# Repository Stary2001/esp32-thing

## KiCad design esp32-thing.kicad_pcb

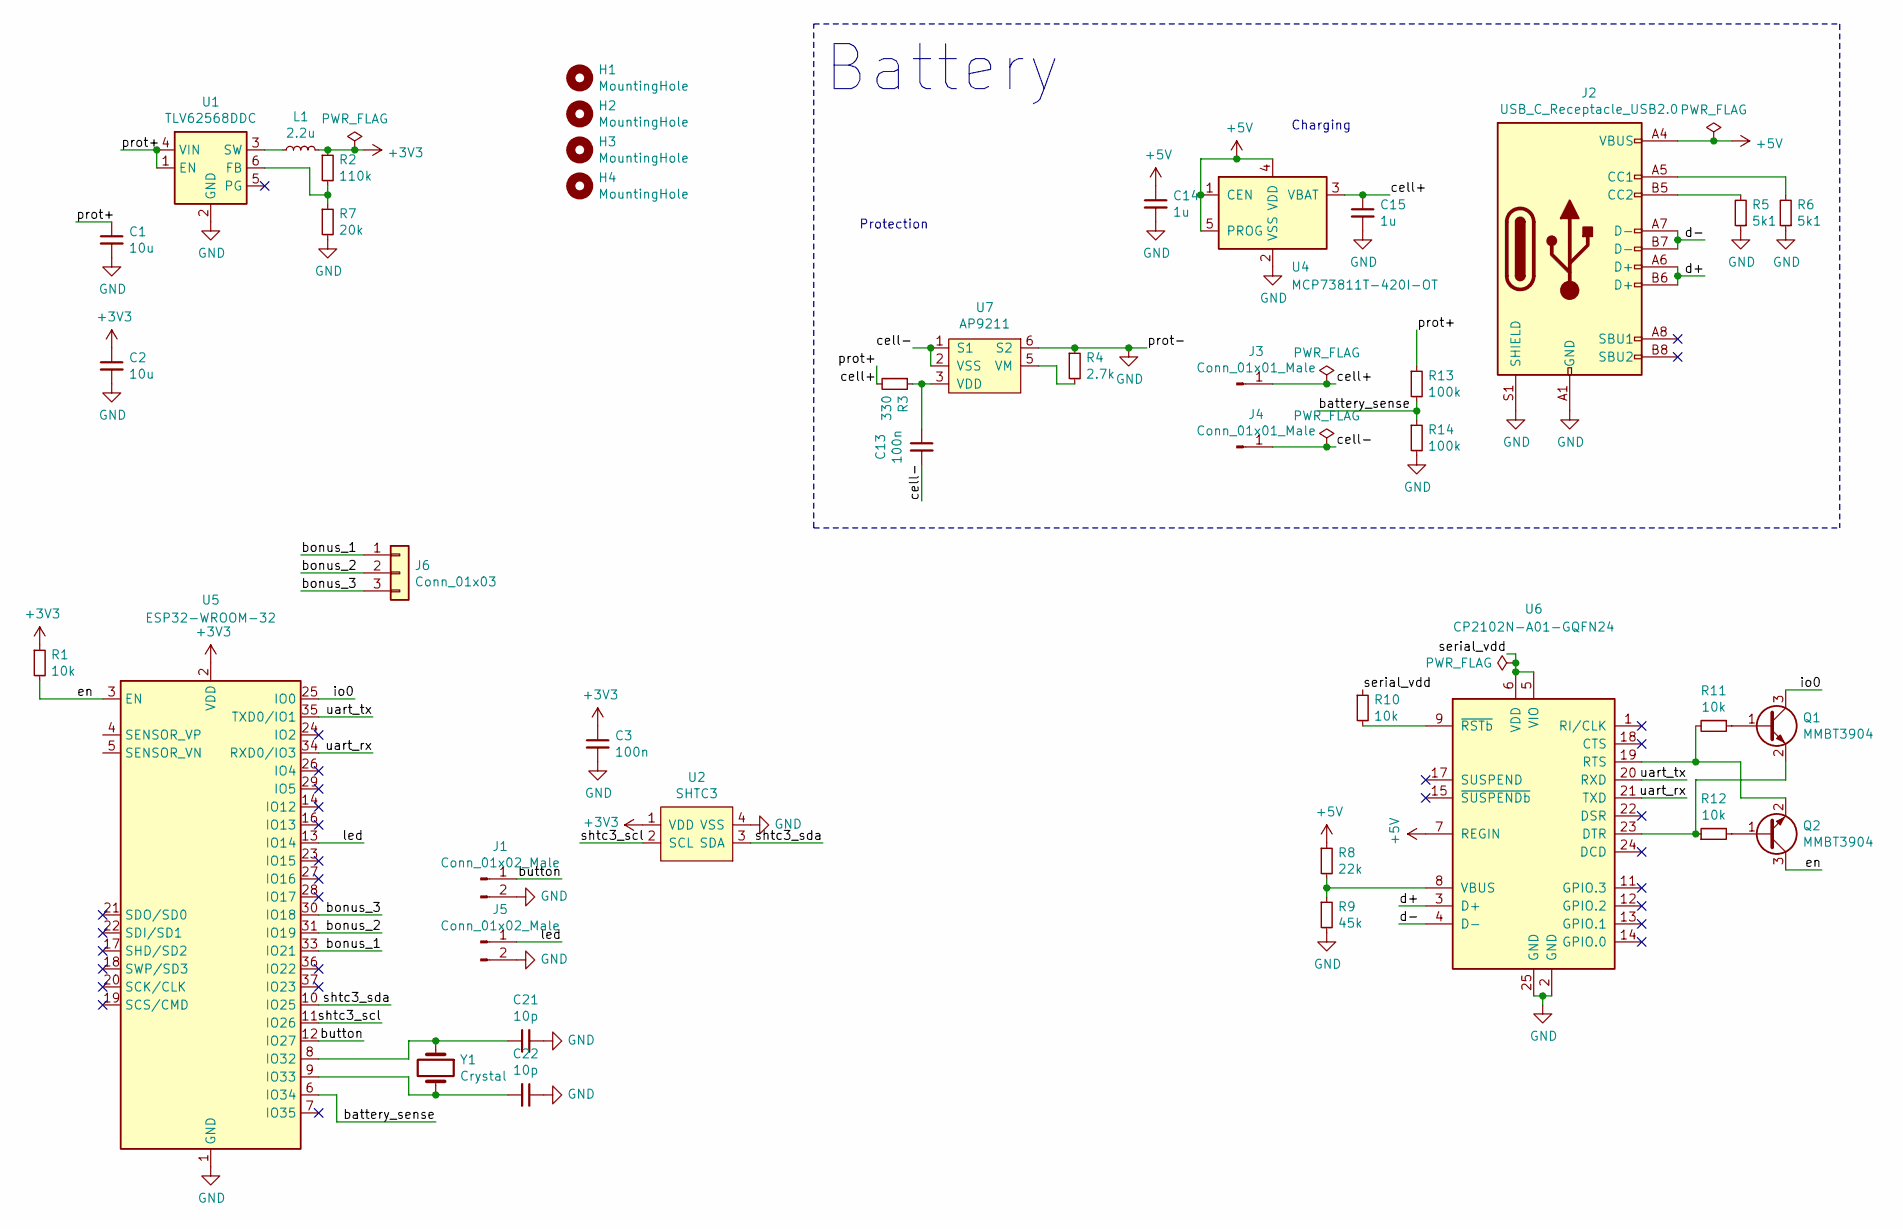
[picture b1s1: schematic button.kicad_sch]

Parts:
C1, C2: 10u; C_0603_1608Metric_Pad1.08x0.95mm_HandSolder
C3: 100n; C_0603_1608Metric
C13: 100n; C_0603_1608Metric_Pad1.08x0.95mm_HandSolder
C14, C15: 1u; C_0603_1608Metric_Pad1.08x0.95mm_HandSolder
C21, C22: 10p; C_0603_1608Metric_Pad1.08x0.95mm_HandSolder
H1, H2, H3, H4: MountingHole; MountingHole_3.2mm_M3
J1, J5: Conn_01x02_Male; PinHeader_1x02_P2.54mm_Vertical
J2: USB_C_Receptacle_USB2.0; USB_C_Receptacle_XKB_U262-16XN-4BVC11
J3, J4: Conn_01x01_Male; SolderWire-0.75sqmm_1x01_D1.25mm_OD2.3mm
J6: Conn_01x03; PinSocket_1x03_P2.54mm_Vertical
L1: 2.2u; L_1008_2520Metric
Q1, Q2: MMBT3904; SOT-23
R1, R10, R11, R12: 10k; R_0603_1608Metric_Pad0.98x0.95mm_HandSolder
R2: 110k; R_0603_1608Metric_Pad0.98x0.95mm_HandSolder
R3: 330; R_0603_1608Metric_Pad0.98x0.95mm_HandSolder
R4: 2.7k; R_0603_1608Metric_Pad0.98x0.95mm_HandSolder
R5, R6: 5k1; R_0603_1608Metric_Pad0.98x0.95mm_HandSolder
R7: 20k; R_0603_1608Metric_Pad0.98x0.95mm_HandSolder
R8: 22k; R_0603_1608Metric_Pad0.98x0.95mm_HandSolder
R9: 45k; R_0603_1608Metric_Pad0.98x0.95mm_HandSolder
R13, R14: 100k; R_0603_1608Metric_Pad0.98x0.95mm_HandSolder
U1: TLV62568DDC; SOT-23-6
U2: SHTC3
U4: MCP73811T-420I-OT; SOT-23-5
U5: ESP32-WROOM-32
U6: CP2102N-A01-GQFN24; QFN-24-1EP_4x4mm_P0.5mm_EP2.6x2.6mm
U7: AP9211; Diodes_UDFN2030-6_Type-C
Y1: Crystal; Crystal_SMD_3215-2Pin_3.2x1.5mm

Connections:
+3V3: C2.1, C3.1, L1.2, R1.1, R2.1, U2.1 (VDD), U5.2 (VDD)
+5V: C14.1, J2.A4 (VBUS), J2.A9 (VBUS), J2.B4 (VBUS), J2.B9 (VBUS), R8.1, U4.1 (CEN), U4.4 (VDD), U4.5 (PROG), U6.7 (REGIN)
/battery_sense: R13.2, R14.1, U5.6 (IO34)
/bonus_1: J6.1, U5.33 (IO21)
/bonus_2: J6.2, U5.31 (IO19)
/bonus_3: J6.3, U5.30 (IO18)
/button: J1.1, U5.12 (IO27)
/cell+: C1.1, C15.1, J3.1, R3.2, R13.1, U1.1 (EN), U1.4 (VIN), U4.3 (VBAT)
/cell-: C13.2, J4.1, U7.1 (S1), U7.2 (VSS)
/d+: J2.A6 (D+), J2.B6 (D+), U6.3 (D+)
/d-: J2.A7 (D-), J2.B7 (D-), U6.4 (D-)
/en: Q2.3 (C), R1.2, U5.3 (EN)
/io0: Q1.3 (C), U5.25 (IO0)
/led: J5.1, U5.13 (IO14)
/serial_vdd: R10.1, U6.5 (VIO), U6.6 (VDD)
/shtc3_scl: U2.2 (SCL), U5.11 (IO26)
/shtc3_sda: U2.3 (SDA), U5.10 (IO25)
/uart_rx: U5.34 (RXD0/IO3), U6.21 (TXD)
/uart_tx: U5.35 (TXD0/IO1), U6.20 (RXD)
GND: C1.2, C2.2, C3.2, C14.2, C15.2, C21.2, C22.1, J1.2, J2.A1 (GND), J2.A12 (GND), J2.B1 (GND), J2.B12 (GND), J2.S1 (SHIELD), J5.2, R4.1, R5.1, R6.1, R7.2, R9.2, R14.2, U1.2 (GND), U2.4 (VSS), U2.5 (VSS), U4.2 (VSS), U5.1 (GND), U5.15 (GND), U5.38 (GND), U5.39 (GND), U6.2 (GND), U6.25 (GND), U7.6 (S2)
unnamed: C13.1, R3.1, U7.3 (VDD)
unnamed: C21.1, U5.8 (IO32), Y1.1
unnamed: C22.2, U5.9 (IO33), Y1.2
unnamed: J2.A5 (CC1), R6.2
unnamed: J2.B5 (CC2), R5.2
unnamed: L1.1, U1.3 (SW)
unnamed: Q1.1 (B), R11.1
unnamed: Q1.2 (E), R12.1, U6.23 (DTR)
unnamed: Q2.1 (B), R12.2
unnamed: Q2.2 (E), R11.2, U6.19 (RTS)
unnamed: R2.2, R7.1, U1.6 (FB)
unnamed: R4.2, U7.5 (VM)
unnamed: R8.2, R9.1, U6.8 (VBUS)
unnamed: R10.2, U6.9 (~RSTb)

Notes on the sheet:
Battery
Protection
Charging

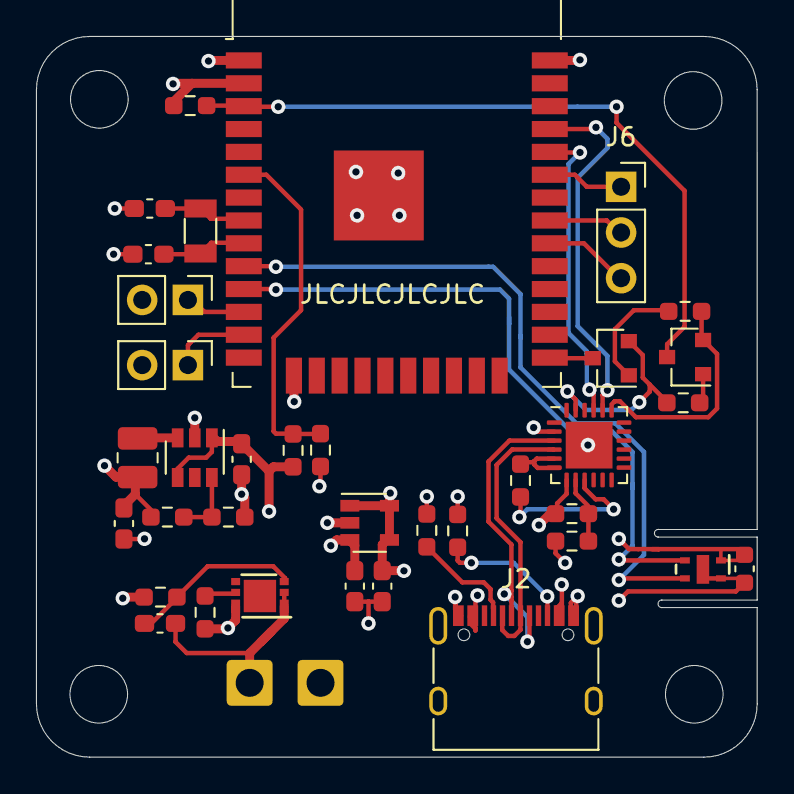
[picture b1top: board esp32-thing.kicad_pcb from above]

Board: 4 copper layers, 40.0 x 40.0 mm, 42 parts (0 on the bottom side), 34 nets.

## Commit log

2021-04-21 add initial revision
2021-04-25 rename
